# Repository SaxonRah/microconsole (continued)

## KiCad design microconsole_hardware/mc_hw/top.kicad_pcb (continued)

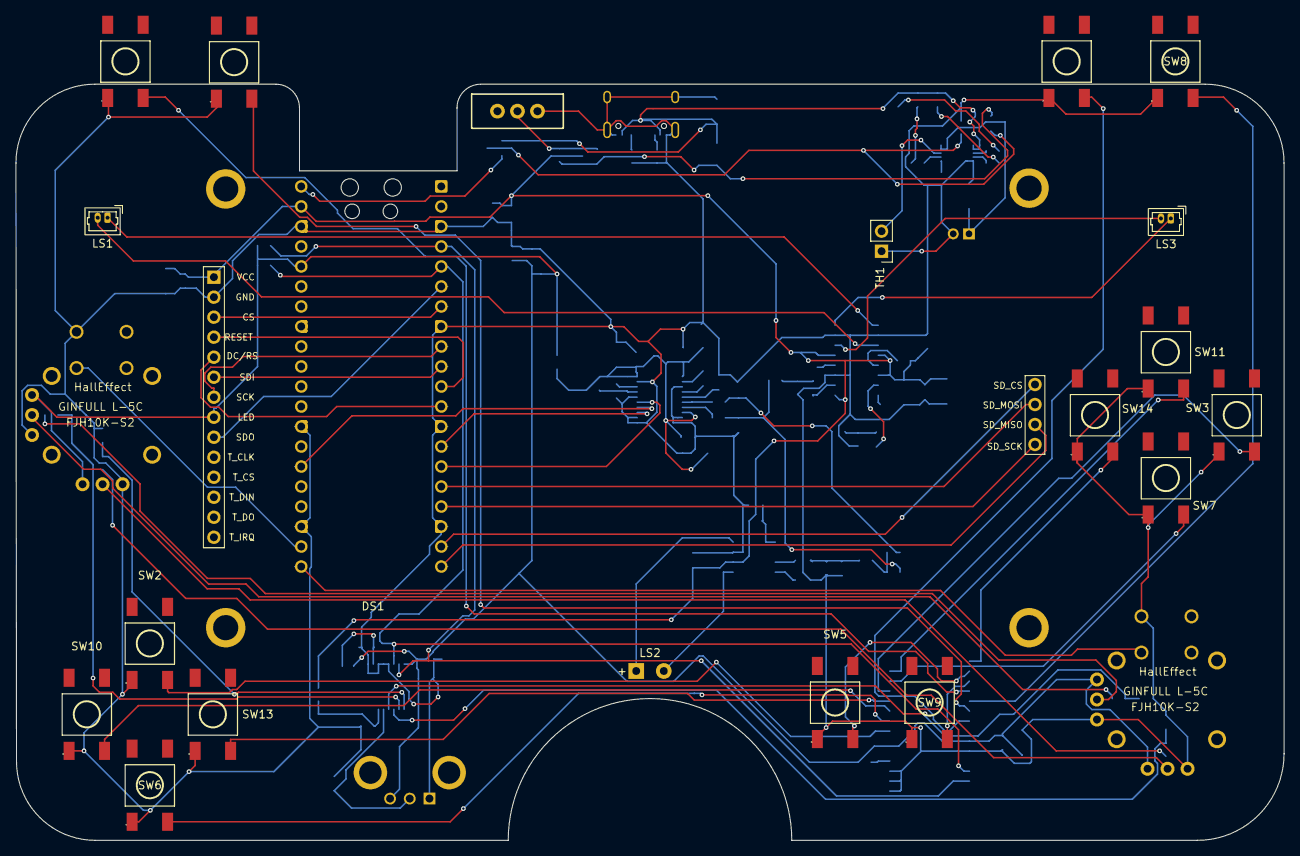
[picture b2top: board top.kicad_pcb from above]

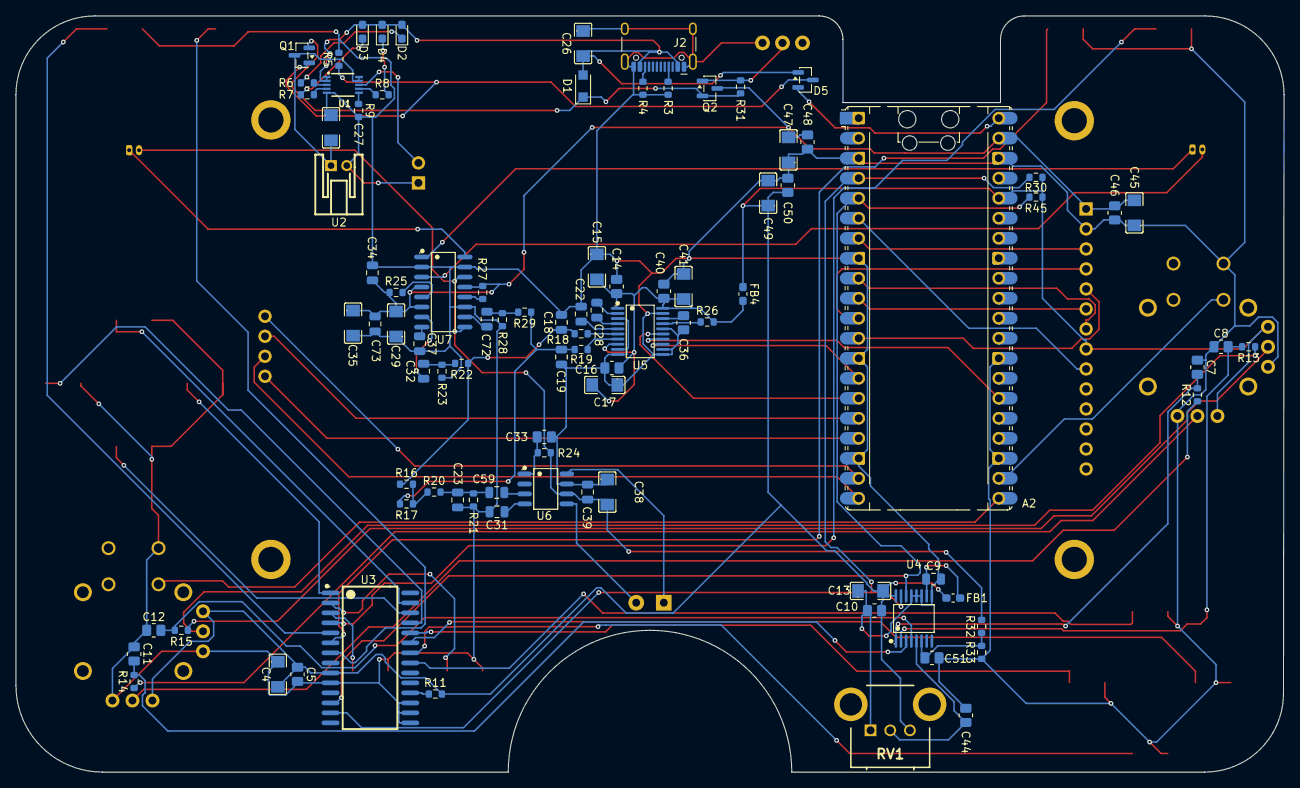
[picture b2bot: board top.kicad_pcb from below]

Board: 2 copper layers, 161.0 x 96.0 mm, 115 parts (93 on the bottom side), 90 nets.

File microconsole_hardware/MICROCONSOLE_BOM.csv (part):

Scope,Subsystem,Status,Qty,References,Description,Value,Manufacturer,MPN,Alternate_Manufacturer,Alternate_MPN,Footprint,Voltage,Tolerance,Power,Datasheet,Notes,Source_Commit
BOARD,Audio,FROZEN,2,C18 C19,2.2nF capacitor,2.2nF,KEMET,C0805C222J5GECTU,,,Capacitor_SMD:C_0805_2012Metric,50V,5%,,,,d4a7d9ce329572b1c15564d63b3878c15175a040
BOARD,Audio,FROZEN,2,C22 C28,2.2uF capacitor,2.2uF,Murata Electronics,GRM21BR71C225KA12L,,,Capacitor_SMD:C_0805_2012Metric,16V,10%,,,,d4a7d9ce329572b1c15564d63b3878c15175a040
BOARD,Audio,FROZEN,1,C23,33nF capacitor,33nF,KEMET,C0805C333K5RECAUTO,,,Capacitor_SMD:C_0805_2012Metric,50V,10%,,,,d4a7d9ce329572b1c15564d63b3878c15175a040
BOARD,Audio,FROZEN,2,C31 C59,0.22uF capacitor,0.22uF,TDK,C2012X7R1H224K125AA,,,Capacitor_SMD:C_0805_2012Metric,50V,10%,,,,d4a7d9ce329572b1c15564d63b3878c15175a040
BOARD,Audio,FROZEN,2,C32 C72,0.47uF capacitor,0.47uF,TDK,C2012X7R1H474K125AB,,,Capacitor_SMD:C_0805_2012Metric,50V,10%,,,,d4a7d9ce329572b1c15564d63b3878c15175a040
BOARD,Audio,FROZEN,2,LS1 LS3 (board headers),Molex PicoBlade 1x02 1.25 mm vertical board header,53047-0210,Molex,53047-0210,,,Connector_Molex:Molex_PicoBlade_53047-0210_1x02_P1.25mm_Vertical,,,,,Physical PCB part represented by LS1/LS3 footprints; mates to the speaker lead housings.,d4a7d9ce329572b1c15564d63b3878c15175a040
BOARD,Audio,FROZEN,2,R18 R19,470 resistor,470,YAGEO,RC0603FR-07470RL,,,Resistor_SMD:R_0603_1608Metric,,1%,0.1W,,,d4a7d9ce329572b1c15564d63b3878c15175a040
BOARD,Audio,FROZEN,1,R20,33k resistor,33k,YAGEO,RC0603FR-0733KL,,,Resistor_SMD:R_0603_1608Metric,,1%,0.1W,,,d4a7d9ce329572b1c15564d63b3878c15175a040
BOARD,Audio,FROZEN,2,R22 R29,27k resistor,27k,YAGEO,RC0603FR-0727KL,,,Resistor_SMD:R_0603_1608Metric,,1%,0.1W,,,d4a7d9ce329572b1c15564d63b3878c15175a040
BOARD,Audio,FROZEN,2,R23 R28,2k resistor,2k,YAGEO,RC0603FR-072KL,,,Resistor_SMD:R_0603_1608Metric,,1%,0.1W,,,d4a7d9ce329572b1c15564d63b3878c15175a040
BOARD,Audio,FROZEN,1,RV1,10k linear through-hole potentiometer,10k Lin,Bourns,PTV09A-2015F-B103,,,project_parts:PTV09A2015FB103,,1%,0.1W,https://componentsearchengine.com/Datasheets/1/PTV09A-2015F-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,,d4a7d9ce329572b1c15564d63b3878c15175a040
BOARD,Audio,FROZEN,1,U5,PCM5102A stereo DAC,PCM5102APWR,Texas Instruments,PCM5102APWR,,,project_parts:TSSOP-20_L6.5-W4.4-P0.65-LS6.4-BL,,,,https://lcsc.com/product-detail/Audio-A-D-Converter-ICs_TI_P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,,d4a7d9ce329572b1c15564d63b3878c15175a040
BOARD,Audio,FROZEN,1,U6,PAM8302A mono amplifier,PAM8302AADCR,Diodes Incorporated,PAM8302AADCR,,,project_parts:SOP-8_L4.9-W3.9-P1.27-LS6.0-BL,,,,https://lcsc.com/product-detail/Audio-OpAmps_DIODES_PAM8302A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,,d4a7d9ce329572b1c15564d63b3878c15175a040
BOARD,Audio,FROZEN,1,U7,PAM8406 stereo amplifier,PAM8406DR,Diodes Incorporated,PAM8406DR,,,project_parts:SOIC-16_L9.9-W3.9-P1.27-LS6.0-BL,,,,https://lcsc.com/product-detail/Audio-OpAmps_DIODES_PAM8406D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,,d4a7d9ce329572b1c15564d63b3878c15175a040
BOARD,Audio+Battery,FROZEN,3,R5 R24 R31,100k resistor,100k,YAGEO,RC0603FR-07100KL,,,Resistor_SMD:R_0603_1608Metric,,1%,0.1W,,,d4a7d9ce329572b1c15564d63b3878c15175a040
BOARD,Audio+Battery+Buttons+PicoScreen,FROZEN,13,C4 C13 C15 C17 C26 C27 C29 C35 C38 C41 C45 C47 C49,10uF capacitor,1206ZD106KAT2A,KYOCERA AVX,1206ZD106KAT2A,,,project_parts:C1206,10V,10%,,,,d4a7d9ce329572b1c15564d63b3878c15175a040
BOARD,Audio+Battery+Buttons+PicoScreen,FROZEN,16,C5 C7 C8 C10 C11 C12 C14 C16 C33 C36 C40 C44 C46 C48 C50 C51,100nF capacitor,100nF 50V X7R,KEMET,C0805C104K5RAC7210,,,project_parts:C_0805_2012Metric_KEMET_IPC-B,50V,10%,,,,d4a7d9ce329572b1c15564d63b3878c15175a040
BOARD,Audio+Buttons,FROZEN,5,C9 C34 C37 C39 C73,1uF capacitor,1uF,Murata Electronics,GRM21BR71C105KA01L,,,Capacitor_SMD:C_0805_2012Metric,16V,10%,,,,d4a7d9ce329572b1c15564d63b3878c15175a040
BOARD,Audio+Buttons,FROZEN,2,FB1 FB4,Ferrite bead,MPZ1608S601ATA00 FerriteBead,TDK,MPZ1608S601ATA00,,,Inductor_SMD:L_0603_1608Metric_Pad1.05x0.95mm_HandSolder,,,,https://product.tdk.com/system/files/dam/doc/product/emc/emc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,,d4a7d9ce329572b1c15564d63b3878c15175a040
BOARD,Audio+Buttons,FROZEN,6,R11 R16 R17 R25 R26 R27,10k resistor,10k,YAGEO,RC0603FR-0710KL,,,Resistor_SMD:R_0603_1608Metric,,1%,0.1W,,,d4a7d9ce329572b1c15564d63b3878c15175a040
BOARD,Audio+PicoScreen,FROZEN,3,R21 R30 R45,4.7k resistor,4.7k,YAGEO,RC0603FR-074K7L,,,Resistor_SMD:R_0603_1608Metric,,1%,0.1W,,,d4a7d9ce329572b1c15564d63b3878c15175a040
BOARD,Battery,FROZEN,1,D1,Schottky diode,PMEG40T30ER Schottky,Nexperia,PMEG40T30ERX,,,Diode_SMD:Nexperia_CFP3_SOD-123W,,,,https://assets.nexperia.com/documents/data-sheet/PMEG40T30ER.pdf,,d4a7d9ce329572b1c15564d63b3878c15175a040
BOARD,Battery,FROZEN,1,D2,Red LED,LED - RED,Lite-On Inc.,LTST-C190KRKT,,,LED_SMD:LED_0603_1608Metric_Pad1.05x0.95mm_HandSolder,,,,,,d4a7d9ce329572b1c15564d63b3878c15175a040
BOARD,Battery,FROZEN,1,D3,Green LED,LED - GREEN,Lite-On Inc.,LTST-C190KGKT,,,LED_SMD:LED_0603_1608Metric_Pad1.05x0.95mm_HandSolder,,,,,,d4a7d9ce329572b1c15564d63b3878c15175a040
BOARD,Battery,FROZEN,1,D4,Orange LED,LED - ORANGE,Lite-On Inc.,LTST-C190KFKT,,,LED_SMD:LED_0603_1608Metric_Pad1.05x0.95mm_HandSolder,,,,,,d4a7d9ce329572b1c15564d63b3878c15175a040
BOARD,Battery,FROZEN,1,D5,Dual common-cathode Schottky diode,BAT54C,Diodes Incorporated,BAT54C-7-F,,,Package_TO_SOT_SMD:SOT-23,,,,http://www.diodes.com/_files/datasheets/ds11005.pdf,,d4a7d9ce329572b1c15564d63b3878c15175a040
BOARD,Battery,FROZEN,2,Q1 Q2,P-channel MOSFET,DMP2035U-7,Diodes Incorporated,DMP2035U-7,,,Package_TO_SOT_SMD:SOT-23,,,,https://www.diodes.com/datasheet/download/DMP2035U.pdf,,d4a7d9ce329572b1c15564d63b3878c15175a040
BOARD,Battery,FROZEN,2,R3 R4,5.1k resistor,5.1k,YAGEO,RC0603FR-075K1L,,,Resistor_SMD:R_0603_1608Metric,,1%,0.1W,,,d4a7d9ce329572b1c15564d63b3878c15175a040
BOARD,Battery,FROZEN,1,R9,3.32k resistor,3.32k,YAGEO,RC0603FR-073K32L,,,Resistor_SMD:R_0603_1608Metric,,1%,0.1W,,,d4a7d9ce329572b1c15564d63b3878c15175a040
BOARD,Battery,FROZEN,1,R32,68k resistor,68k,YAGEO,RC0603FR-0768KL,,,Resistor_SMD:R_0603_1608Metric,,1%,0.1W,,,d4a7d9ce329572b1c15564d63b3878c15175a040
BOARD,Battery,FROZEN,1,R33,82k resistor,82k,YAGEO,RC0603FR-0782KL,,,Resistor_SMD:R_0603_1608Metric,,1%,0.1W,,,d4a7d9ce329572b1c15564d63b3878c15175a040
BOARD,Battery,FROZEN,1,SW19,SPDT slide switch,SPDT_Slide_PTH_11.6x4.0mm,SparkFun Electronics,COM-00102,,,PCM_SparkFun-Switch:Slide_SPDT_PTH_11.6x4.0mm,,,,https://www.sparkfun.com/datasheets/Components/Buttons/P040040c.pdf,,d4a7d9ce329572b1c15564d63b3878c15175a040
BOARD,Battery,TBD,1,TH1 (board header),1x02 2.54 mm vertical header for wired thermistor,1x02 2.54mm,,,,,Connector_PinHeader_2.54mm:PinHeader_1x02_P2.54mm_Vertical,,,,,Exact header manufacturer/MPN not yet frozen. Omit this row if TH1 is soldered directly into the two plated holes.,d4a7d9ce329572b1c15564d63b3878c15175a040
BOARD,Battery,FROZEN,1,U1,Li-Ion/Li-Po charge controller,MCP73833-FCI/UN,Microchip Technology,MCP73833-FCI/UN,,,PCM_SparkFun-Semiconductor-Standard:MSOP-10_3x3mm_P0.5mm,,,,https://ww1.microchip.com/downloads/en/DeviceDoc/22005b.pdf,,d4a7d9ce329572b1c15564d63b3878c15175a040
BOARD,Battery,FROZEN,1,U2,JST PH right-angle 2-pin header,S2B-PH-K-S,JST,S2B-PH-K-S(LF)(SN),,,project_parts:CONN-TH_S2B-PH-K-S-LF-SN,,,,https://lcsc.com/product-detail/PH-Connectors_JST-Sales-Amer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,,d4a7d9ce329572b1c15564d63b3878c15175a040
BOARD,Battery+Buttons,FROZEN,7,R6 R7 R8 R12 R13 R14 R15,1k resistor,1k,YAGEO,RC0603FR-071KL,,,Resistor_SMD:R_0603_1608Metric,,1%,0.1W,,,d4a7d9ce329572b1c15564d63b3878c15175a040
BOARD,Buttons,FROZEN,14,SW2 SW3 SW4 SW5 SW6 SW7 SW8 SW9 SW10 SW11 SW12 SW13 SW14 SW15,Tactile switch,TL3301NF160QG,E-Switch,TL3301NF160QG,,,project_parts:KEY-SMD_4P-L6.0-W6.0-P4.50-LS10.0,,,,https://www.lcsc.com/datasheet/C273526.pdf,,d4a7d9ce329572b1c15564d63b3878c15175a040
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
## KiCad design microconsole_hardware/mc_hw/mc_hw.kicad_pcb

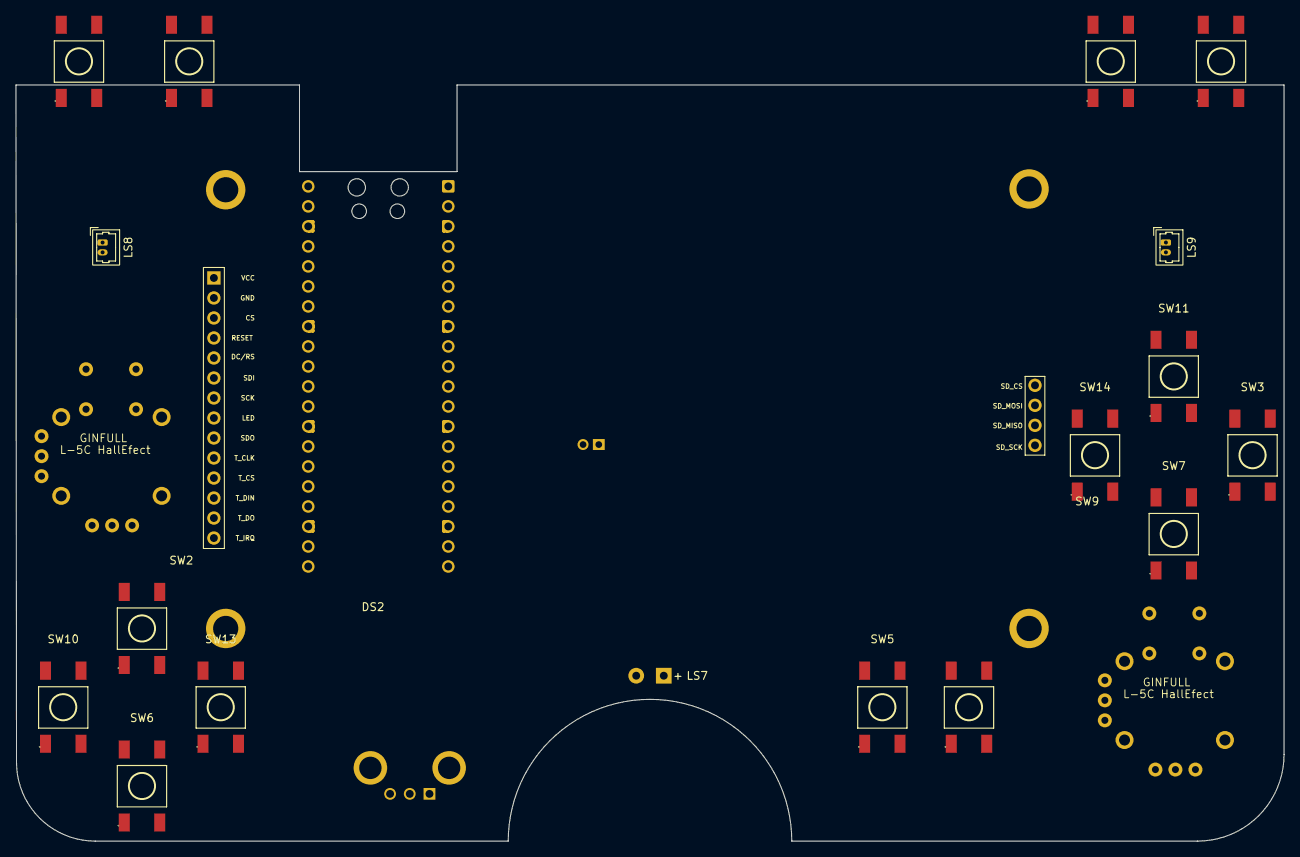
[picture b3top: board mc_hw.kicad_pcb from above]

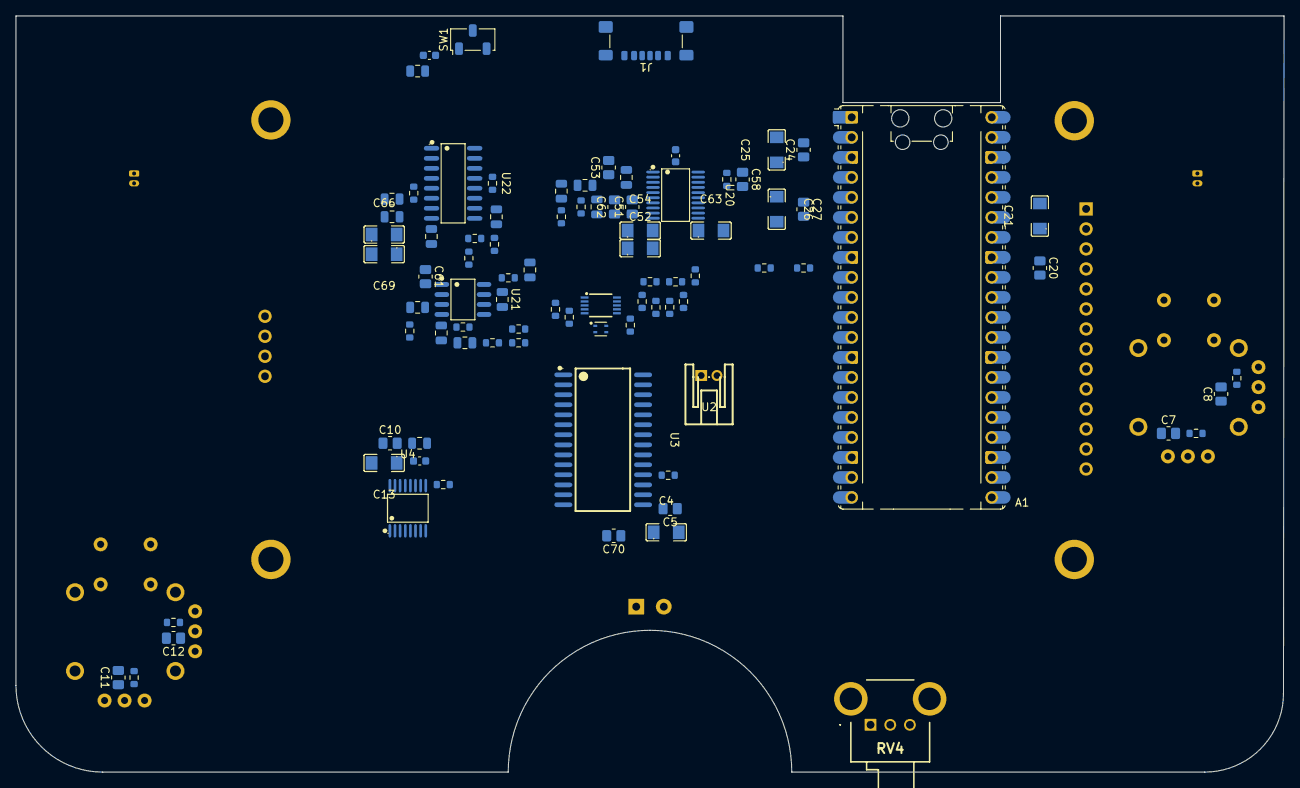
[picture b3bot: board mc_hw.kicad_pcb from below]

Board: 2 copper layers, 161.0 x 96.0 mm, 107 parts (87 on the bottom side), 87 nets, no tracks yet.

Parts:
A1: RaspberryPi_Pico; RaspberryPi_Pico_Common_Unspecified
C3, C6: 2.2uF; C_0805_2012Metric
C4, C13, C21, C25, C26, C52, C54, C63, C66, C69: 1206ZD106KAT2A; C1206
C5, C7, C8, C10, C11, C12, C20, C24, C27, C51, C53, C58, C61, C62, C70: 100nF 50V X7R; C_0805_2012Metric_KEMET_IPC-B
C9, C65, C68, C71, C73: 1uF; C_0805_2012Metric
C55, C56: 2.2nF; C_0805_2012Metric
C57: 33nF; C_0805_2012Metric
C59, C60: 0.22uF; C_0805_2012Metric
C64: 10uF; C_0805_2012Metric
C67, C72: 0.47uF; C_0805_2012Metric
D1: D_Schottky; Sensirion_DFN-4_1.5x1.5mm_P0.8mm_SHT4x_NoCentralPad
D2: LED - RED; R_0603_1608Metric
D3: LED - GREEN; R_0603_1608Metric
D4: LED - ORANGE; R_0603_1608Metric
DS2: MSP4021; LCD_MSP4021_4.0in_SPI_ST7796_1x14_P2.54mm
FB1, FB2, FB3: FerriteBead_Small; C_0603_1608Metric
J1: USB_C_Receptacle_USB2.0_16P; USB_C_Receptacle_GCT_USB4135-GF-A_6P_TopMnt_Horizontal
LS7: 8R 3W; Speaker_WirePads_1x02_P3.50mm_D1.0mm
LS8, LS9: 8R 1W; Molex_PicoBlade_53047-0210_1x02_P1.25mm_Vertical
R1, R2: 4.7k; R_0603_1608Metric
R3, R4: 5.1k OHM; R_0603_1608Metric
R5: 100k; R_0603_1608Metric
R6, R7, R8: 1k; R_0603_1608Metric
R9: 2k; R_0603_1608Metric
R10, R11: 10k; R_0603_1608Metric
R12, R13, R14, R15: 1k OHM; R_0603_1608Metric
R31, R32, R38, R41, R42: 10k OHM; R_0603_1608Metric
R33, R34: 470 OHM; R_0603_1608Metric
R35: 33k OHM; R_0603_1608Metric
R36: 4.7k OHM; R_0603_1608Metric
R37: 100k OHM; R_0603_1608Metric
R39, R44: 22k OHM; R_0603_1608Metric
R40, R43: 2.2k OHM; R_0603_1608Metric
RV4: 10k Lin; PTV09A2015FB103
SW1: SW_Nidec_CAS-120A1; Nidec_Copal_CAS-120A
SW2, SW3, SW4, SW5, SW6, SW7, SW8, SW9, SW10, SW11, SW12, SW13, SW14, SW15: TL3301NF160QG; KEY-SMD_4P-L6.0-W6.0-P4.50-LS10.0
SW16, SW17: Joystick; GINFULL HallEffect Joystick PTH
U1: MCP73833_MSOP; MSOP-10_3x3mm_P0.5mm
U2: S2B-PH-K-S; CONN-TH_S2B-PH-K-S-LF-SN
U3: MCP23017-E/SO; SOIC-28_L18.0-W7.5-P1.27-LS10.3-BL
U4: ADS7828E/2K5; TSSOP-16_L5.0-W4.4-P0.65-LS6.4-BL
U20: PCM5102APWR; TSSOP-20_L6.5-W4.4-P0.65-LS6.4-BL
U21: PAM8302AADCR; SOP-8_L4.9-W3.9-P1.27-LS6.0-BL
U22: PAM8406DR; SOIC-16_L9.9-W3.9-P1.27-LS6.0-BL

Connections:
3v3: A1.36 (3V3), C4.2, C5.1, C10.1, C13.2, C24.1, C25.1, DS2.8 (LED), FB1.1, FB3.1, R1.1, R2.1, R11.2, RV4.3 (CW), SW16.VCC, SW17.VCC, U3.9 (VDD), U4.16 (+VDD)
3v3_ADC: C9.1, FB1.2, U4.10 (REFIN/REFOUT)
3v3_AUDIO: C51.2, C53.2, C62.2, FB3.2, R38.1, U20.1 (CPVDD), U20.8 (AVDD), U20.20 (DVDD)
AMP_VDD: C64.1, C65.1, C66.2, C68.2, C69.1, C73.2, FB2.2, R37.1, R41.2, R42.1, U21.6 (VDD), U22.4 (PVDDL), U22.6 (VDD), U22.9 (MODE), U22.13 (PVDDR)
BAT+: U1.9 (V_{BAT}), U1.10 (V_{BAT}), U2.1
CENTER_FEED: C57.1, C59.1, R35.1, R36.1
CENTER_MIX: R31.1, R32.2, R35.2
DAC_L: C55.1, R31.2, R33.2, R39.2
DAC_R: C56.1, R32.1, R34.2, R44.2
FILTERED - IO0 / Left Stick X: C7.2, R12.1, U4.1 (CH0)
FILTERED - IO1 / Left Stick Y: C8.2, R13.1, U4.2 (CH1)
FILTERED - IO2 / Right Stick X: C11.2, R14.1, U4.3 (CH2)
FILTERED - IO3 / Right Stick Y: C12.2, R15.1, U4.4 (CH3)
GND: A1.3 (GND), A1.8 (GND), A1.13 (GND), A1.18 (GND), A1.23 (GND), A1.28 (GND), A1.38 (GND), C4.1, C5.2, C6.2, C7.1, C8.1, C9.2, C10.2, C11.1, C12.1, C13.1, C20.2, C21.1, C24.2, C25.2, C26.1, C27.1, C51.1, C52.1, C52.2, C53.1, C54.1, C54.2, C55.2, C56.2, C57.2, C58.1, C60.2, C61.1, C62.1, C63.1, C63.2, C64.2, C65.2, C66.1, C68.1, C69.2, C70.1, C71.2, C73.1, DS2.2 (GND), J1.A12 (GND), J1.B12 (GND), J1.SH (SHIELD), R3.2, R4.1, R5.2, R9.2, R10.2, R36.2, R40.2, R43.2, RV4.1 (CCW), SW2.1, SW3.1, SW4.1, SW5.1, SW6.1, SW7.1, SW8.1, SW9.1, SW10.1, SW11.1, SW12.1, SW13.1, SW14.1, SW15.1, SW16.GND, SW17.GND, U1.5 (VSS), U3.10 (VSS), U3.15 (A0), U3.16 (A1), U3.17 (A2), U4.9 (GND), U4.11 (COM), U4.12 (A0), U4.13 (A1), U20.3 (CPGND), U20.9 (AGND), U20.10 (DEMP), U20.11 (FLT), U20.12 (SCK), U20.16 (FMT), U20.19 (DGND), U21.7 (GND), U22.2 (PGNDL), U22.11 (GND), U22.15 (PGNDR)
GPIO2 / MCP|ADC SDA: A1.4 (GPIO2), R1.2, U3.13 (SDA), U4.15 (SDA)
GPIO3 / MCP|ADC SCL: A1.5 (GPIO3), R2.2, U3.12 (SCL), U4.14 (SCL)
GPIO4 / LCD MISO: A1.6 (GPIO4), DS2.9 (SDO(MISO))
GPIO5 / LCD CS: A1.7 (GPIO5), DS2.3 (CS)
GPIO6 / LCD SCK: A1.9 (GPIO6), DS2.7 (SCK)
GPIO7 / LCD MOSI: A1.10 (GPIO7), DS2.6 (SDI(MOSI))
GPIO8 / LCD RESET: A1.11 (GPIO8), DS2.4 (RESET)
GPIO9 / LCD DC: A1.12 (GPIO9), DS2.5 (DC/RS)
GPIO10 / MAX BCLK: A1.14 (GPIO10), U20.13 (BCK)
GPIO11 / MAX LRC: A1.15 (GPIO11), U20.15 (LRCK)
GPIO12 / SD MISO: A1.16 (GPIO12), DS2.17 (SD_MISO)
GPIO13 / SD CS: A1.17 (GPIO13), DS2.15 (SD_CS)
GPIO14 / SD SCK: A1.19 (GPIO14), DS2.18 (SD_SCK)
GPIO15 / SD MOSI: A1.20 (GPIO15), DS2.16 (SD_MOSI)
GPIO16 / Left Stick: A1.21 (GPIO16), SW16.Select
GPIO17 / Right Stick: A1.22 (GPIO17), SW17.Select
GPIO20 / MAX DIN: A1.26 (GPIO20), U20.14 (DIN)
IO0 / Left Stick X: R12.2, SW16.Horizontal
IO1 / Left Stick Y: R13.2, SW16.Vertical
IO2 / Right Stick X: R14.2, SW17.Horizontal
IO3 / Right Stick Y: R15.2, SW17.Vertical
MCP GPA0 / DPAD - UP: SW2.4, U3.21 (GPA0)
MCP GPA1 / DPAD - DOWN: SW6.4, U3.22 (GPA1)
MCP GPA2 / DPAD - LEFT: SW10.4, U3.23 (GPA2)
MCP GPA3 / DPAD - RIGHT: SW13.4, U3.24 (GPA3)
MCP GPA4 / A: SW3.4, U3.25 (GPA4)
MCP GPA5 / B: SW7.4, U3.26 (GPA5)
MCP GPA6 / X: SW11.4, U3.27 (GPA6)
MCP GPB0 / Y: SW14.4, U3.1 (GPB0)
MCP GPB1 / SELECT: SW5.4, U3.2 (GPB1)
MCP GPB2 / START: SW9.4, U3.3 (GPB2)
MCP GPB3 / L1: SW4.4, U3.4 (GPB3)
MCP GPB4 / R1: SW8.4, U3.5 (GPB4)
MCP GPB5 / L2: SW12.4, U3.6 (GPB5)
MCP GPB6 / R2: SW15.4, U3.7 (GPB6)
MCP RESET: R11.1, U3.18 (~RESET)
unnamed: C67.2, R39.1, R40.1
unnamed: C72.2, R43.1, R44.1
unnamed: D2.1 (K), R6.2
unnamed: D3.1 (K), R7.2
unnamed: D4.1 (K), R8.2
unnamed: J1.A5 (CC1), R3.1
unnamed: J1.B5 (CC2), R4.2
unnamed: LS7.1 (+), U21.8 (VO-)
unnamed: LS7.2 (-), U21.5 (VO+)
unnamed: LS8.1 (+_(red)), U22.1 (+OUT_L)
unnamed: LS8.2 (-_(black)), U22.3 (-OUT_L)
unnamed: LS9.1 (+_(red)), U22.16 (+OUT_R)
unnamed: LS9.2 (-_(black)), U22.14 (-OUT_R)
unnamed: R9.1, U1.6 (PROG)
unnamed: R6.1, U1.3 (STAT1)
unnamed: R7.1, U1.4 (STAT2)
unnamed: R10.1, U1.8 (THERM)
unnamed: R8.1, U1.7 (~PG)
unnamed: C3.2, U20.4 (CAPM)
unnamed: C3.1, U20.2 (CAPP)
unnamed: C58.2, U20.18 (LDOO)
unnamed: R33.1, U20.6 (OUTL)
unnamed: R34.1, U20.7 (OUTR)
unnamed: C6.1, U20.5 (VNEG)
unnamed: R38.2, U20.17 (XSMT)
unnamed: C59.2, U21.3 (IN+)
unnamed: C60.1, U21.4 (IN-)
unnamed: C61.2, R37.2, U21.1 (~SD)
unnamed: C67.1, U22.7 (INL)
unnamed: C72.1, U22.10 (INR)
unnamed: C71.1, U22.8 (VREF)
unnamed: R41.1, U22.5 (~MUTE)
unnamed: R42.2, U22.12 (~SHDN)
SYS_RAW: D1.1 (K), SW1.2 (B)
USB-VBUS: D1.2 (A), D2.2 (A), D3.2 (A), D4.2 (A), J1.A9 (VBUS), J1.B9 (VBUS), R5.1, U1.1 (VDD), U1.2 (VDD)
VOL_ADC: C70.2, RV4.2 (WIPER), U4.5 (CH4)
VSYS_BAT: A1.39 (VSYS), A1.40 (VBUS), C20.1, C21.2, C26.2, C27.2, DS2.1 (VCC), FB2.1, SW1.1 (C)
